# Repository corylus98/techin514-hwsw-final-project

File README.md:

# Final Project - Hardware/Software Lab

## Focus Track
The product is a desktop companion device designed to enhance productivity and well-being while working. It sits beside the user's computer and uses sensors to monitor typing patterns and screen time. By analyzing typing speed and consistency, it identifies whether the user is focused on productive tasks or engaging in non-work-related activities. The device features:
- Focus Level Indicator: A needle-style display that reflects the user's focus level based on typing behavior, encouraging sustained productivity.
- Break Reminder System: An LED light that gently alerts the user when they've been at their screen for too long, promoting healthier work habits through regular breaks.

## Sensor Device
The sensor device combines a vibration sensor and a proximity sensor to enable analysis of focus and screen usage.
- The vibration sensor detects typing actions, analyzing patterns to determine whether the user is typing productively.
- The proximity sensor tracks the user's presence in front of the screen to monitor screen time.

## Display Device
The display device interacts with the user through physical interfaces.
- The button allows the user to turn the device on or off.
- The needle indicator displays productivity levels, calculated based on typing patterns.
- The blinking LED light serves as a reminder to take breaks when screen time becomes excessive.

## Communication

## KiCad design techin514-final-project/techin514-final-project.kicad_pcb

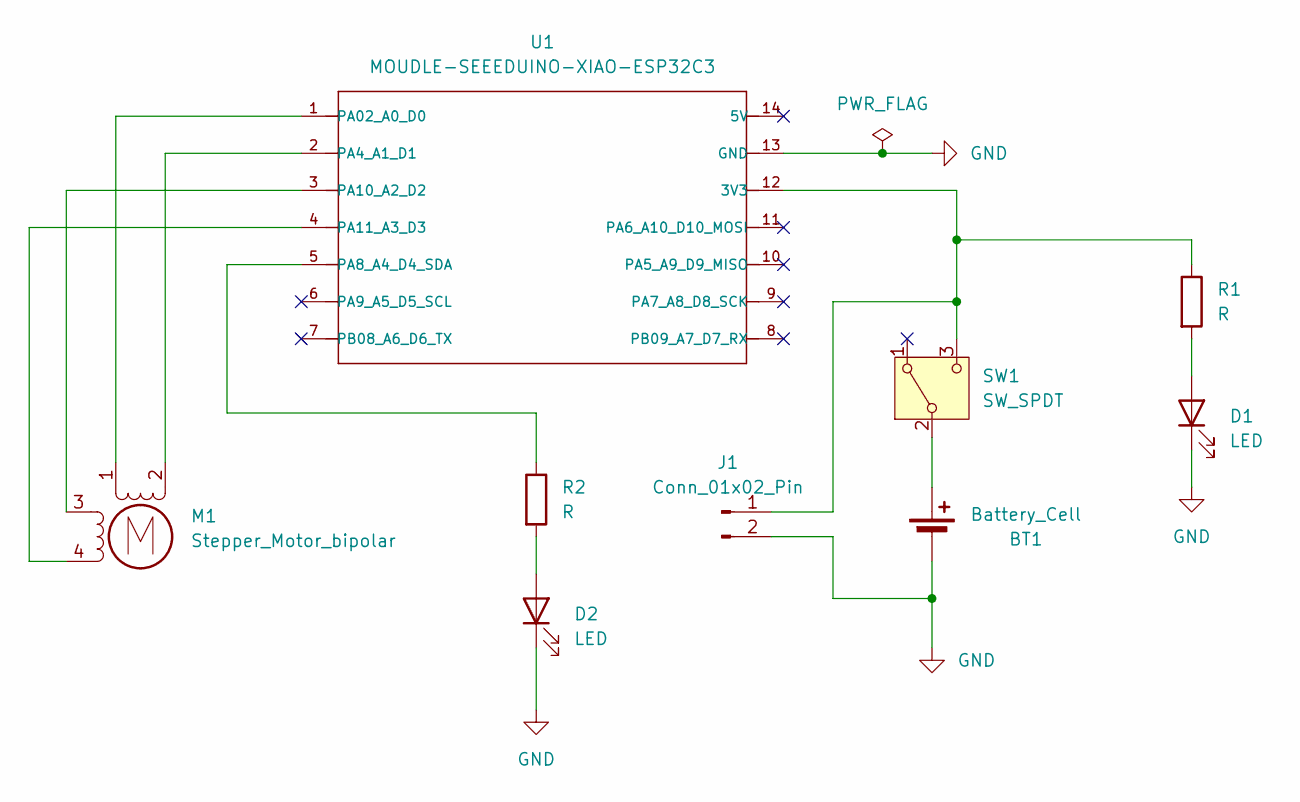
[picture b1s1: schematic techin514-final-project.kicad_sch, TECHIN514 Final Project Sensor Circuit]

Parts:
BT1: Battery_Cell; JST_PH_B2B-PH-K_1x02_P2.00mm_Vertical
D1, D2: LED; LED_D5.0mm
J1: Conn_01x02_Pin; JST_PH_B2B-PH-K_1x02_P2.00mm_Vertical
M1: Stepper_Motor_bipolar; x27_stepper_two_holes
R1, R2: R; R_Axial_DIN0207_L6.3mm_D2.5mm_P15.24mm_Horizontal
SW1: SW_SPDT; JST_EH_B3B-EH-A_1x03_P2.50mm_Vertical
U1: MOUDLE-SEEEDUINO-XIAO-ESP32C3; XIAO_ESP32_SENSE

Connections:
GND: BT1.2 (-), D1.1 (K), D2.1 (K), J1.2, U1.13 (GND)
unnamed: BT1.1 (+), SW1.2 (B)
unnamed: D1.2 (A), R1.2
unnamed: D2.2 (A), R2.2
unnamed: J1.1, R1.1, SW1.3 (C), U1.12 (3V3)
unnamed: M1.2 (-), U1.2 (PA4_A1_D1)
unnamed: M1.1, U1.1 (PA02_A0_D0)
unnamed: R2.1, U1.5 (PA8_A4_D4_SDA)
unnamed: M1.3, U1.3 (PA10_A2_D2)
unnamed: M1.4, U1.4 (PA11_A3_D3)

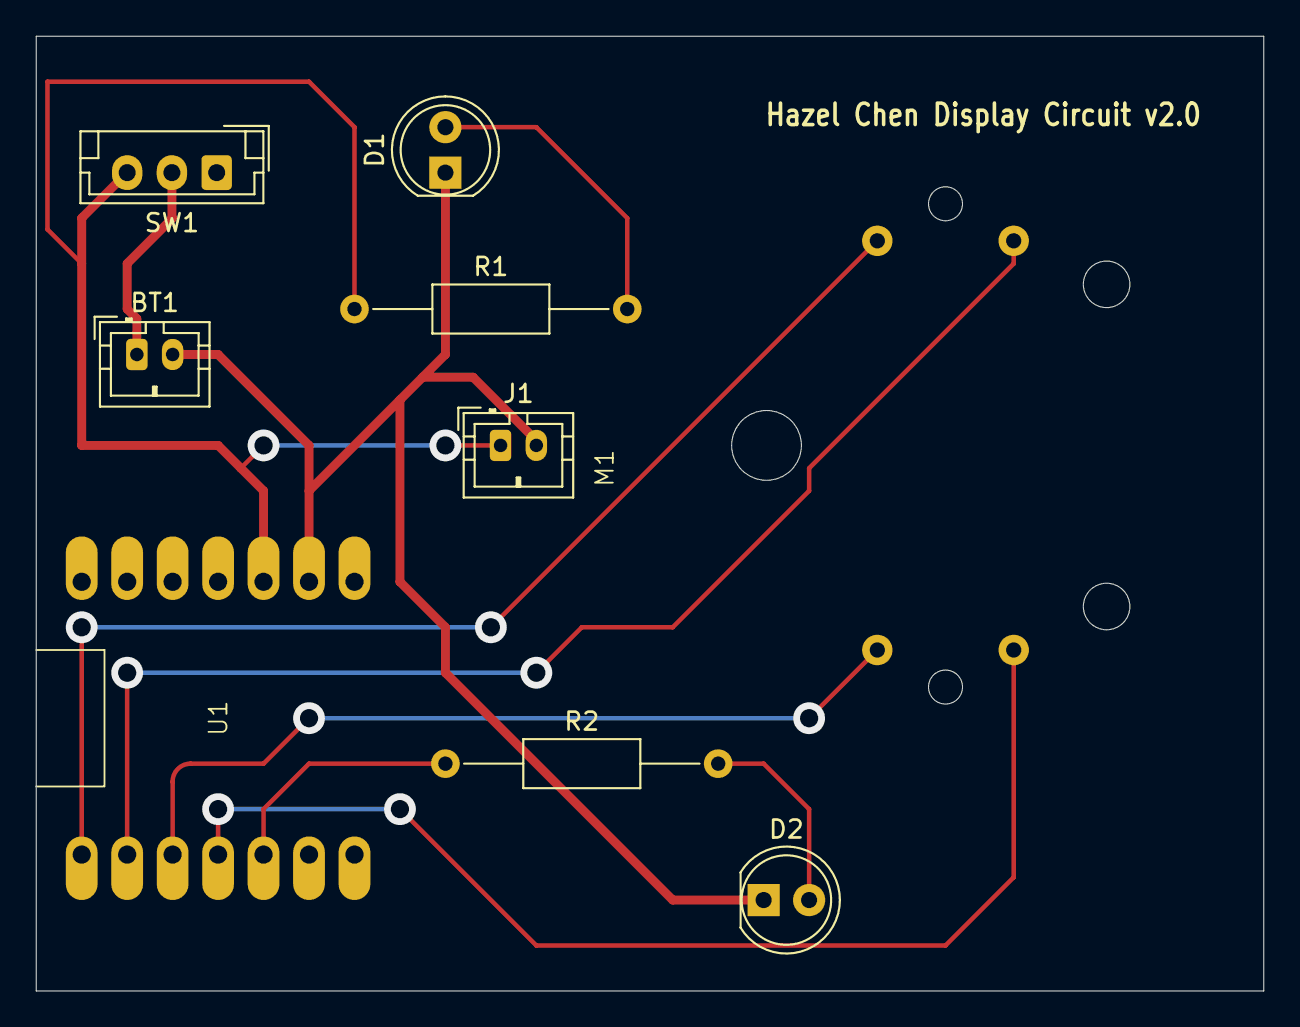
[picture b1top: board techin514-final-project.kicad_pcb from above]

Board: 2 copper layers, 68.6 x 53.3 mm, 9 parts (0 on the bottom side), 10 nets.

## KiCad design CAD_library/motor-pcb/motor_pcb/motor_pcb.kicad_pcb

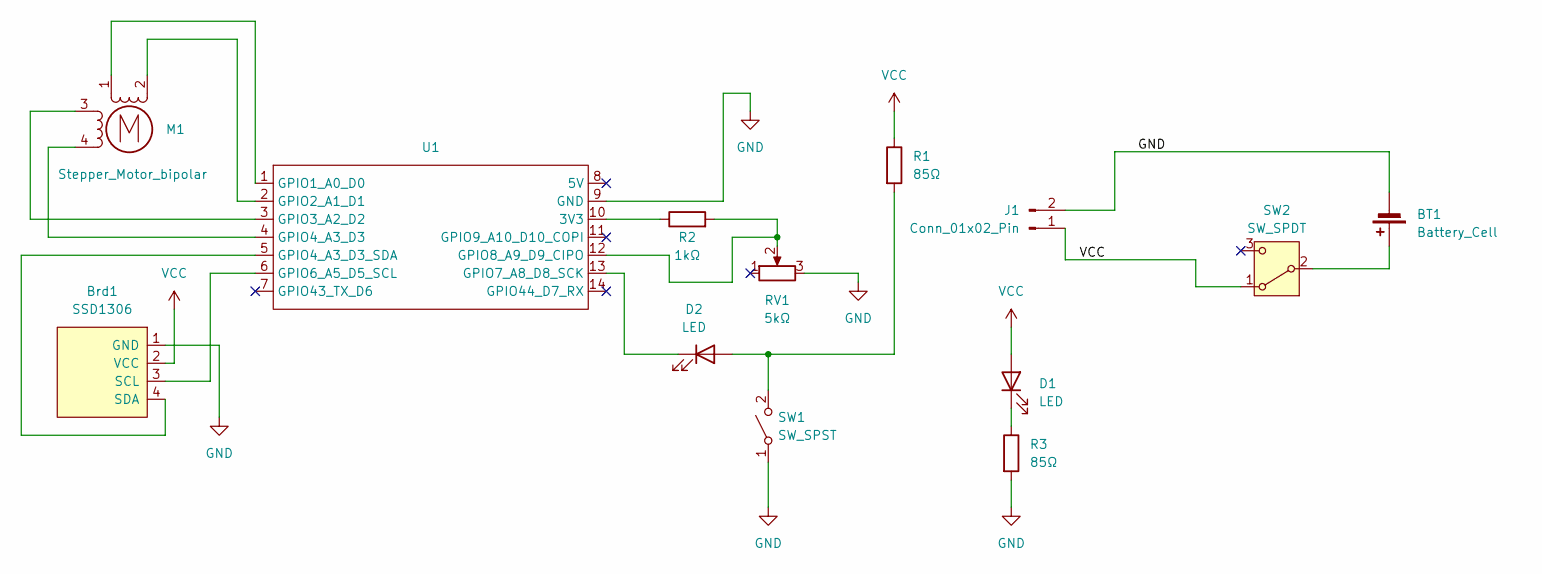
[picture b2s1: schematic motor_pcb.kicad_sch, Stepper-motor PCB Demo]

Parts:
BT1: Battery_Cell; JST_NV_B02P-NV_1x02_P5.00mm_Vertical
Brd1: SSD1306; 128x64OLED
D1, D2: LED; LED_0805_2012Metric_Pad1.15x1.40mm_HandSolder
J1: Conn_01x02_Pin; JST_NV_B02P-NV_1x02_P5.00mm_Vertical
M1: Stepper_Motor_bipolar; x27_stepper
R1, R3: 85Ω; R_0805_2012Metric_Pad1.20x1.40mm_HandSolder
R2: 1kΩ; R_0805_2012Metric_Pad1.20x1.40mm_HandSolder
RV1: 5kΩ; Potentiometer_Piher_T-16H_Single_Horizontal
SW1: SW_SPST; SW_PUSH-12mm
SW2: SW_SPDT; PinHeader_1x03_P2.54mm_Vertical
U1: XIAO_ESP32_SENSE

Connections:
GND: BT1.2 (-), Brd1.1 (GND), J1.2, R3.2, RV1.3, SW1.1 (A), U1.9 (GND)
unnamed: BT1.1 (+), SW2.2 (B)
unnamed: Brd1.3 (SCL), U1.6 (GPIO6_A5_D5_SCL)
unnamed: Brd1.4 (SDA), U1.5 (GPIO4_A3_D3_SDA)
unnamed: D1.1 (K), R3.1
unnamed: D2.2 (A), R1.2, SW1.2 (B)
unnamed: D2.1 (K), U1.13 (GPIO7_A8_D8_SCK)
unnamed: M1.2 (-), U1.2 (GPIO2_A1_D1)
unnamed: R2.1, U1.10 (3V3)
unnamed: M1.1, U1.1 (GPIO1_A0_D0)
unnamed: M1.3, U1.3 (GPIO3_A2_D2)
unnamed: M1.4, U1.4 (GPIO4_A3_D3)
unnamed: R2.2, RV1.2, U1.12 (GPIO8_A9_D9_CIPO)
VCC: Brd1.2 (VCC), D1.2 (A), J1.1, R1.1, SW2.1 (A)

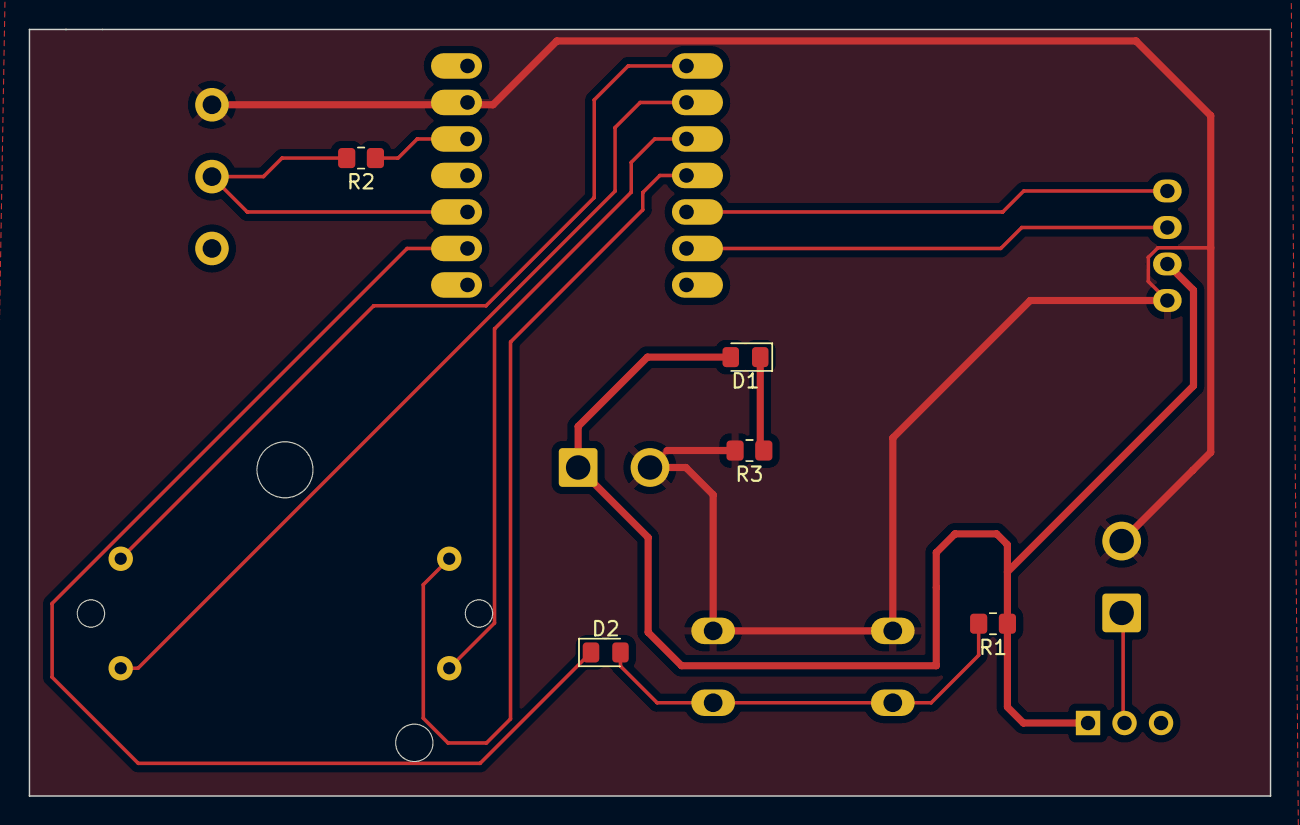
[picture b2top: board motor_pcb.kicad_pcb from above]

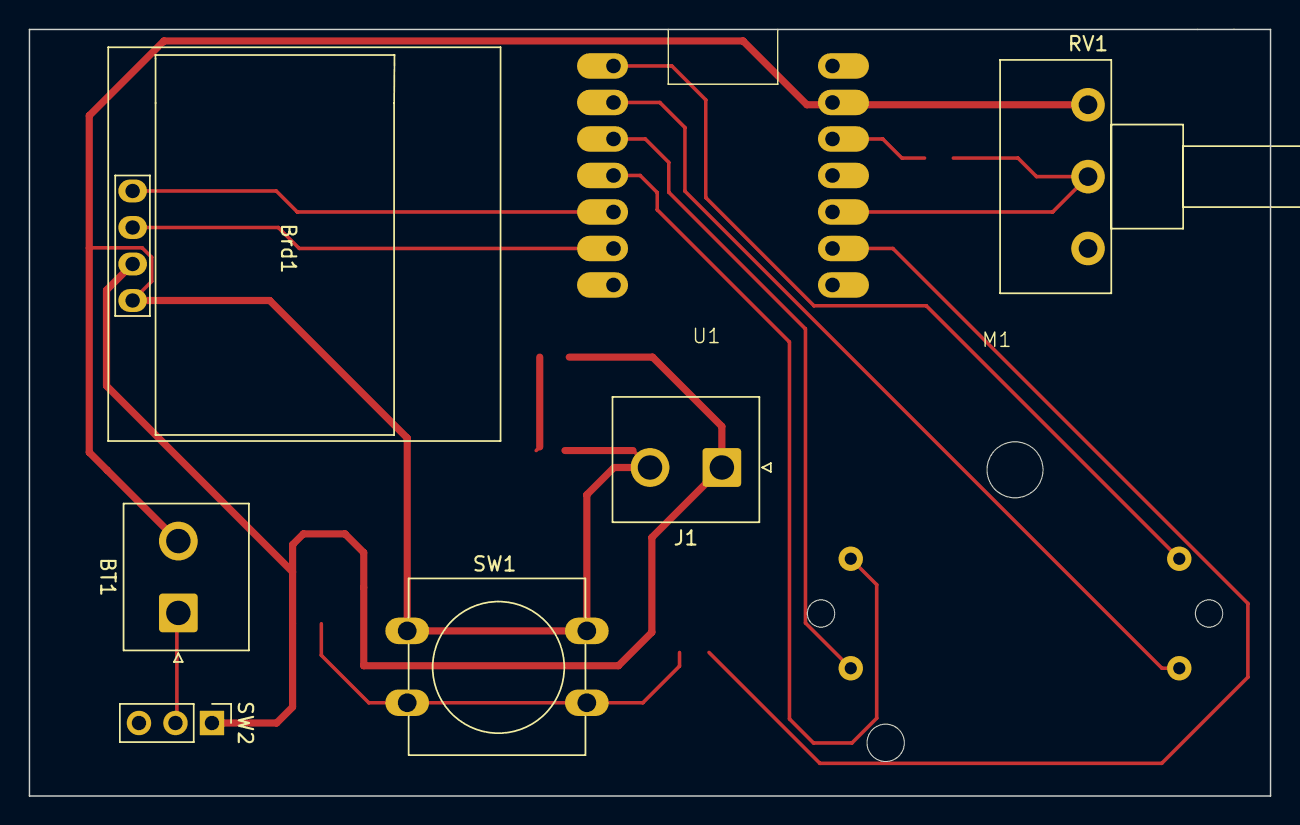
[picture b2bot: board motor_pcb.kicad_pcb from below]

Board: 2 copper layers, 86.4 x 53.3 mm, 13 parts (8 on the bottom side), 14 nets.

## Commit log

2025-01-21 New repo
2025-01-22 Add readme / media
2025-01-22 Add datasheet
2025-01-29 Add KiCAD files
2025-01-29 Modify CAD files
2025-02-14 Add Battery Datasheet
2025-03-11 Add sensor code
2025-03-11 Modify display / client code
